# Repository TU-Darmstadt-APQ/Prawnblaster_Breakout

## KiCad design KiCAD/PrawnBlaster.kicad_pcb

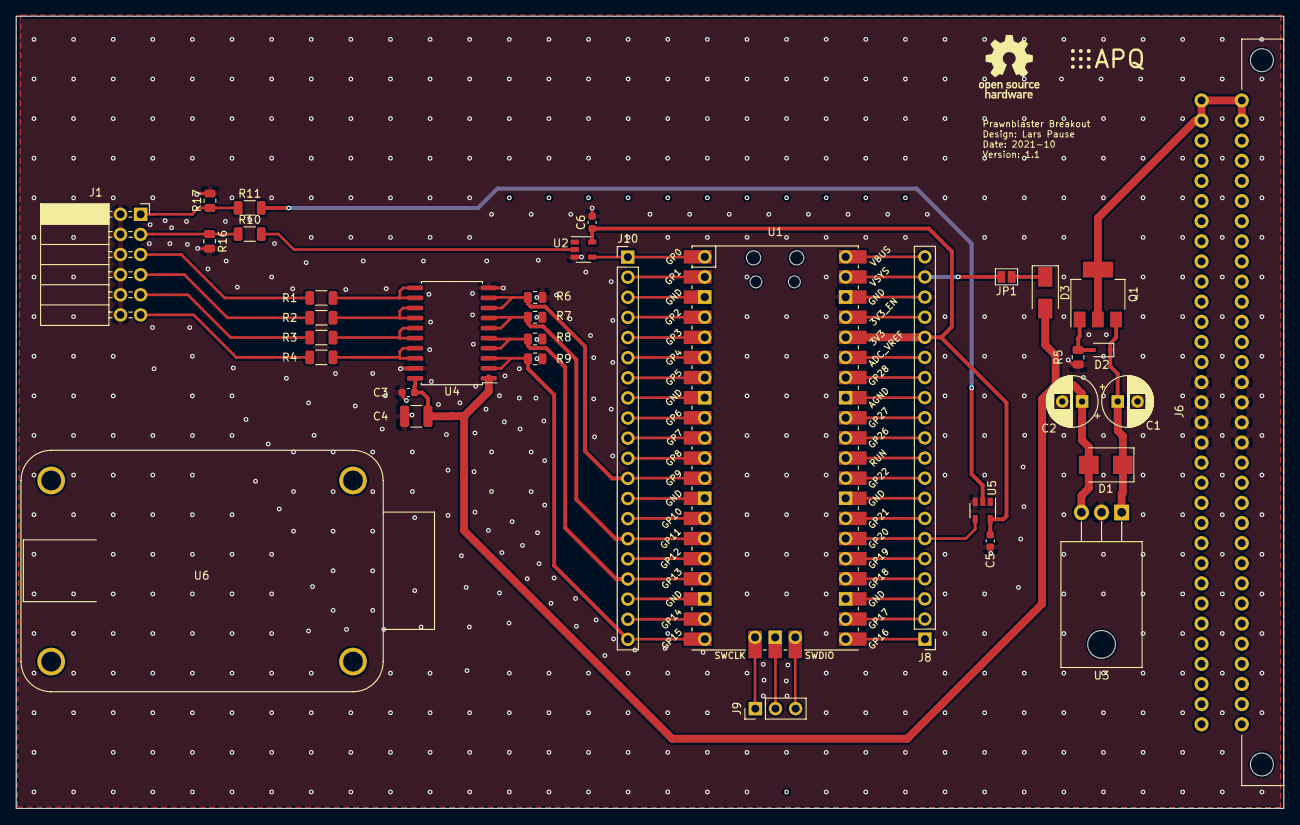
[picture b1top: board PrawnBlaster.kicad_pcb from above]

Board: 2 copper layers, 160.0 x 100.0 mm, 37 parts (0 on the bottom side), 60 nets.

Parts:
C1, C2: 47u; CP_Radial_D6.3mm_P2.50mm
C3, C5, C6: 100n; C_0603_1608Metric
C4: 10u; C_1210_3225Metric
D1: D; D_SMB
D2: MM3Z15VST1G; D_SOD-323
D3: D_Schottky; D_SMA
J1: Conn_02x06_Odd_Even; PinSocket_2x06_P2.54mm_Horizontal
J6: C64AC; Socket_DIN41612-CaseC1-AC-Male-64Pin-2rows
J8, J10: Conn_01x20_Male; PinHeader_1x20_P2.54mm_Vertical
J9: Conn_01x03_Male; PinHeader_1x03_P2.54mm_Vertical
JP1: Jumper_NO_Small; SolderJumper-2_P1.3mm_Open_Pad1.0x1.5mm
LOGO1: Logo_APQ; APQ-Logo_small
LOGO2: Logo_Open_Hardware_Small; OSHW-Logo_7.5x8mm_SilkScreen
Q1: DMP6023LE; SOT-223
R1, R2, R3, R4: 49.9; R_1206_3216Metric
R5: 100k; R_0805_2012Metric
R6, R7, R8, R9: 10k; R_0805_2012Metric
R10, R11: 500; R_1206_3216Metric
R16, R17: 47k; R_0805_2012Metric
U1: Pico; RPi_Pico_SMD_TH
U2: 74LVC1G17; SOT-23-5
U3: 7805; TO-220-3_Horizontal_TabDown
U4: 74ABT245; SOIC-20W_7.5x12.8mm_P1.27mm
U5: 74LVC1G07; SOT-23-5
U6: adafruit_usb_isolator; usb_isolator

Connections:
3_3V_Pico: C5.1, C6.1, J8.16, U1.36, U2.5, U5.5
/Output Buffer/A0: J10.20, R9.1, U1.20, U4.2, U4.3
/Output Buffer/A1: J10.17, R8.1, U1.17, U4.4, U4.5
/Output Buffer/A2: J10.15, R7.1, U1.15, U4.6, U4.7
/Output Buffer/A3: J10.12, R6.1, U1.12, U4.8, U4.9
/Output Buffer/B0: R4.1, U4.17, U4.18
/Output Buffer/B1: R3.1, U4.15, U4.16
/Output Buffer/B2: R2.1, U4.13, U4.14
/Output Buffer/B3: R1.1, U4.11, U4.12
/Output Buffer/Vcc_5V: C2.1, C3.1, C4.1, D1.2, D3.2, U3.3, U4.1, U4.20
/Power Supply/Reverse Polarity Protection/V18: C1.1, D1.1, D2.1, Q1.3, U3.1
/Power Supply/Reverse Polarity Protection/V18_unprot: J6.A1, J6.A2, J6.C1, J6.C2, Q1.2, Q1.4
GND: C1.2, C2.2, C3.2, C4.2, C5.2, C6.2, J1.2, J1.4, J1.6, J1.8, J1.10, J1.12, J6.A15, J6.A16, J6.A17, J6.A18, J6.C15, J6.C16, J6.C17, J6.C18, J8.18, R5.2, R6.2, R7.2, R8.2, R9.2, R16.2, R17.2, U1.38, U2.3, U3.2, U4.10, U4.19, U5.3
unnamed: D2.2, Q1.1, R5.1
unnamed: D3.1, JP1.1
unnamed: J1.1, R11.1, R17.1
unnamed: J1.3, R10.1, R16.1
unnamed: J1.5, R1.2
unnamed: J1.7, R2.2
unnamed: J1.9, R3.2
unnamed: J1.11, R4.2
unnamed: J8.1, U1.21
unnamed: J8.2, U1.22
unnamed: J8.3, U1.23
unnamed: J8.4, U1.24
unnamed: J8.5, U1.25
unnamed: J8.6, U1.26, U5.4
unnamed: J8.7, U1.27
unnamed: J8.8, U1.28
unnamed: J8.9, U1.29
unnamed: J8.10, U1.30
unnamed: J8.11, U1.31
unnamed: J8.12, U1.32
unnamed: J8.13, U1.33
unnamed: J8.14, U1.34
unnamed: J8.15, U1.35
unnamed: J8.17, U1.37
unnamed: J8.19, JP1.2, U1.39
unnamed: J8.20, U1.40
unnamed: J9.1, U1.41
unnamed: J9.2, U1.42
unnamed: J9.3, U1.43
unnamed: J10.1, U1.1, U2.4
unnamed: J10.2, U1.2
unnamed: J10.3, U1.3
unnamed: J10.4, U1.4
unnamed: J10.5, U1.5
unnamed: J10.6, U1.6
unnamed: J10.7, U1.7
unnamed: J10.8, U1.8
unnamed: J10.9, U1.9
unnamed: J10.10, U1.10
unnamed: J10.11, U1.11
unnamed: J10.13, U1.13
unnamed: J10.14, U1.14
unnamed: J10.16, U1.16
unnamed: J10.18, U1.18
unnamed: J10.19, U1.19
unnamed: R10.2, U2.2
unnamed: R11.2, U5.2

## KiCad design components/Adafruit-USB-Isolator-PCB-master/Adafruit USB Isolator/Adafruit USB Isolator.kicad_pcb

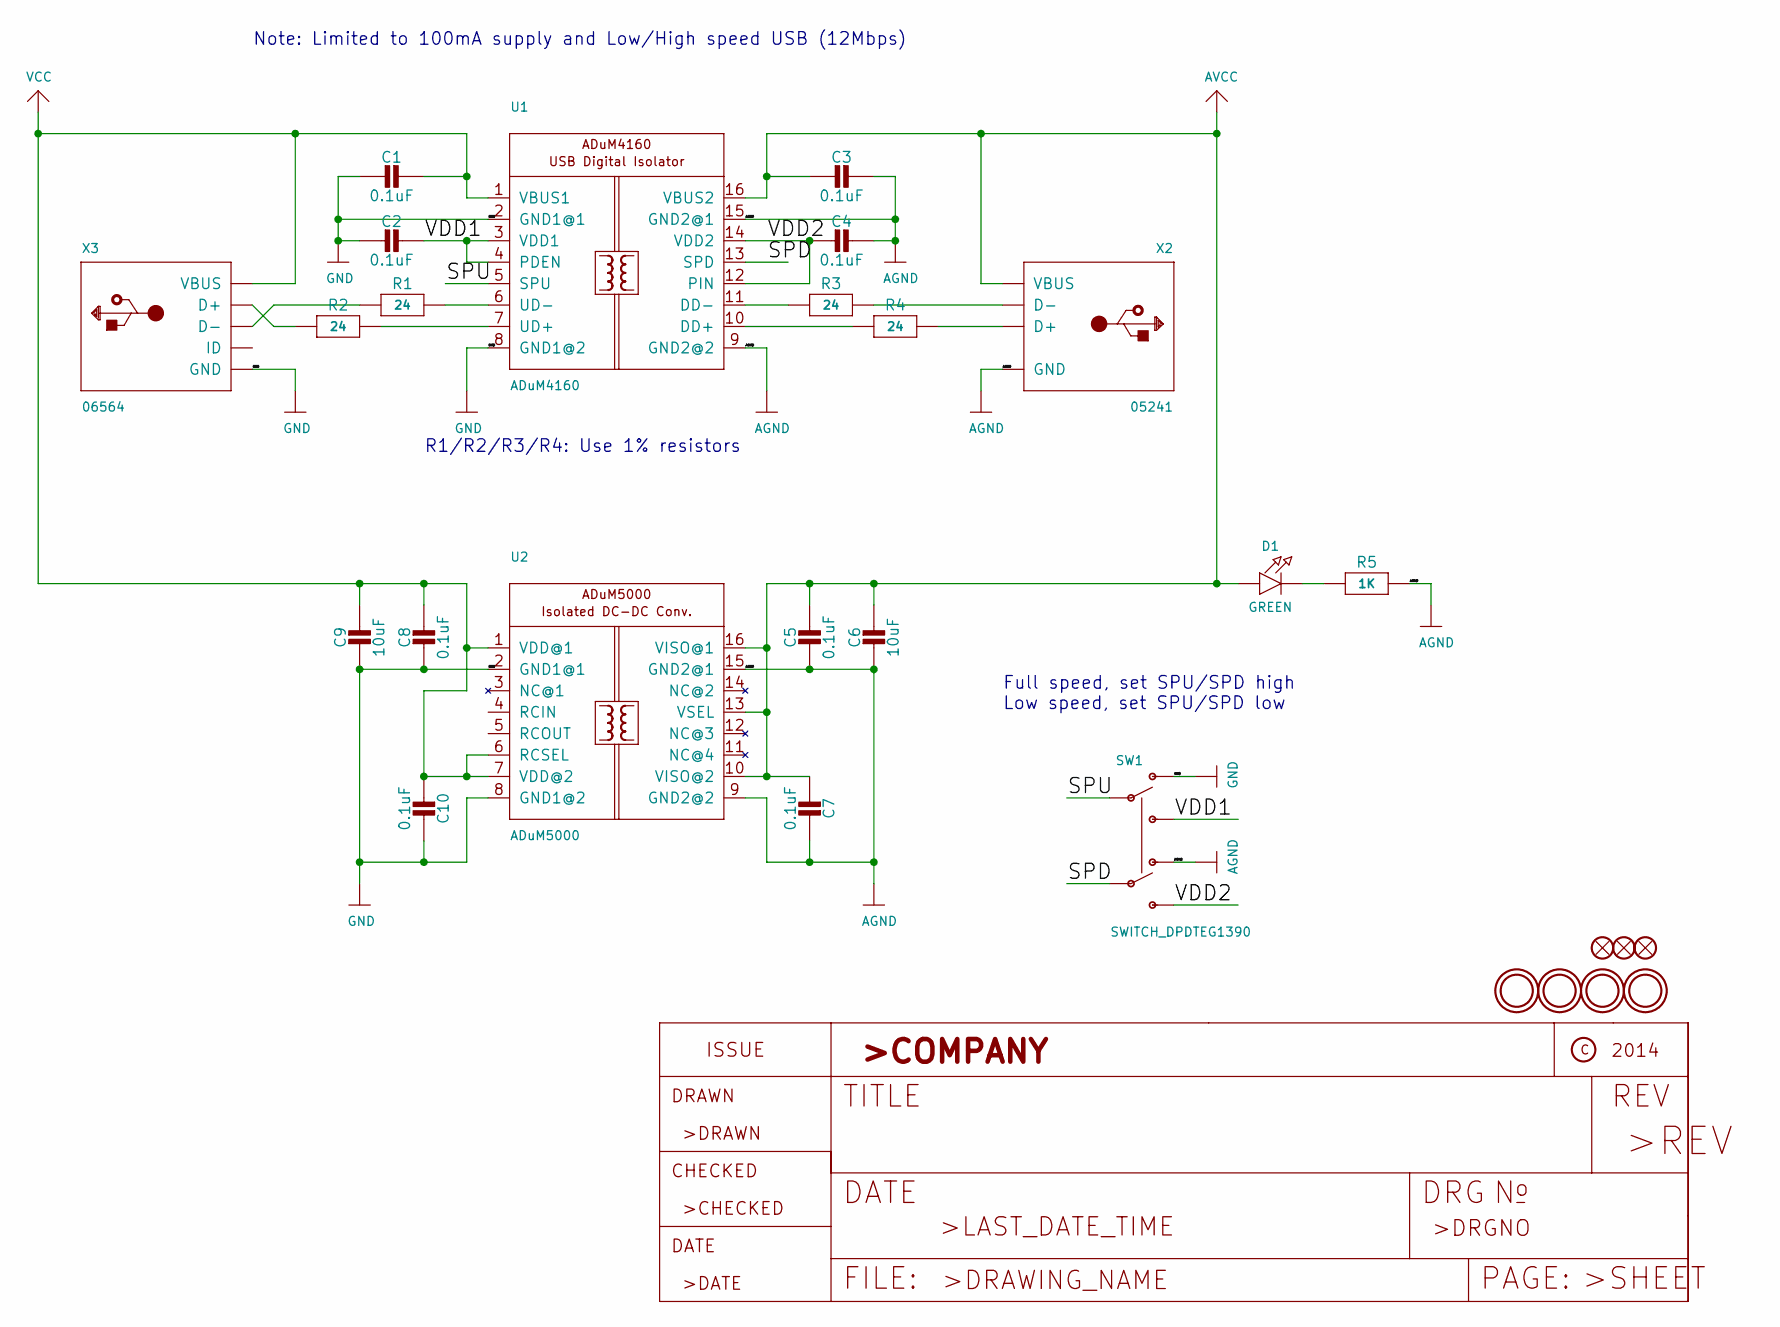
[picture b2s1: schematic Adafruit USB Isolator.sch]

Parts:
C1, C2, C3, C4, C5, C7, C8, C10: 0.1uF; 0805-NO
C6, C9: 10uF; 0805-NO
D1: GREEN; CHIPLED_0805_NOOUTLINE
FID1, FID2, FID3: FIDUCIAL\"\"; FIDUCIAL_1MM
R1, R2, R3: 24; 0805-NO
R4: 24; _0805MP
R5: 1K; 0805-NO
SW1: SWITCH_DPDTEG1390; EG1390
U1: ADuM4160; SOIC16WIDE
U2: ADuM5000; SOIC16WIDE
U$7, U$8, U$9, U$10: MOUNTINGHOLE2.5_THICK; MOUNTINGHOLE_2.5_PLATED_THICK
X2: 05241; USB_HOST-PTH
X3: 06564; USB-MINIB_LARGER

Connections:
/SPD: SW1.P2, U1.13 (SPD)
/SPU: SW1.P1, U1.5 (SPU)
/VDD1: C2.1, SW1.S1, U1.3 (VDD1), U1.4 (PDEN)
/VDD2: C4.2, SW1.S2, U1.12 (PIN), U1.14 (VDD2)
AGND: C3.1, C4.1, C5.2, C6.2, C7.1, R5.2, SW1.O2, U1.9 (GND2@2), U1.15 (GND2@1), U2.9 (GND2@2), U2.15 (GND2@1), X2.GND
AVCC: C3.2, C5.1, C6.1, C7.2, D1.A, U1.16 (VBUS2), U2.10 (VISO@2), U2.13 (VSEL), U2.16 (VISO@1), X2.VBUS
GND: C1.2, C2.2, C8.2, C9.2, C10.1, SW1.O1, U1.2 (GND1@1), U1.8 (GND1@2), U2.2 (GND1@1), U2.8 (GND1@2), X3.GND, X3.GND1 (GND), X3.GND2 (GND), X3.GND3 (GND), X3.GND4 (GND)
unnamed: D1.C, R5.1
unnamed: R1.1, X3.D-
unnamed: R1.2, U1.6 (UD-)
unnamed: R2.1, X3.D+
unnamed: R2.2, U1.7 (UD+)
unnamed: R3.1, U1.11 (DD-)
unnamed: R3.2, X2.D-
unnamed: R4.1, U1.10 (DD+)
unnamed: R4.2, X2.D+
VCC: C1.1, C8.1, C9.1, C10.2, U1.1 (VBUS1), U2.1 (VDD@1), U2.6 (RCSEL), U2.7 (VDD@2), X3.VBUS

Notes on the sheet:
R1/R2/R3/R4: Use 1% resistors
Note: Limited to 100mA supply and Low/High speed USB (12Mbps)
Full speed, set SPU/SPD high Low speed, set SPU/SPD low

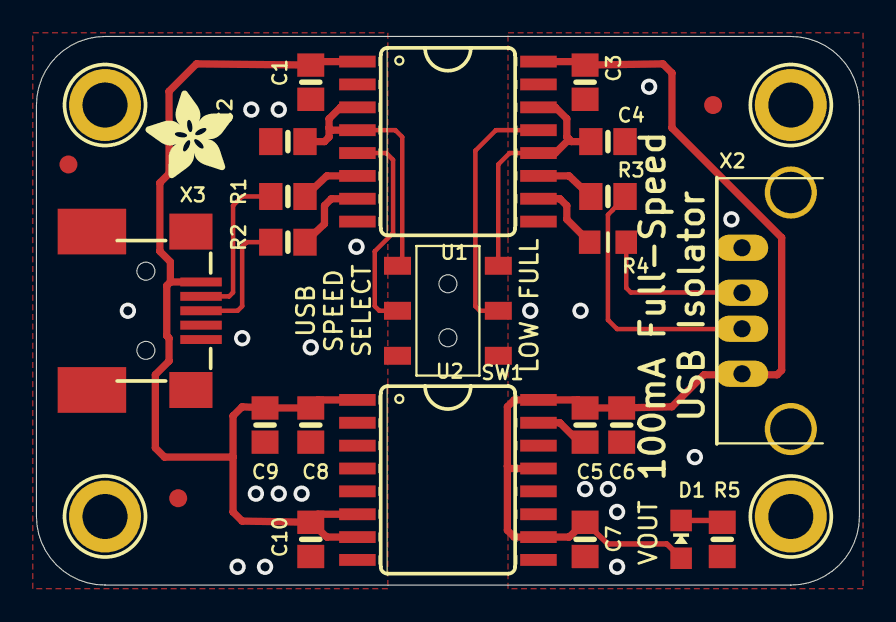
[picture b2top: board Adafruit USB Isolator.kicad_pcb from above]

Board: 2 copper layers, 45.7 x 30.5 mm, 30 parts (0 on the bottom side), 17 nets.

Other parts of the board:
U$14: ADAFRUIT_5MM
U$16: ADAFRUIT_TEXT_30MM

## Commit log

2021-09-16 forked PulseBlaster with 4 outputs
2021-09-16 added pico and external trigger
2021-09-20 Add Pi Pico in project library; create sheets for Pi Pico and ext trig
    Add the Pi Pico library and create sheets for the input buffer (with external trigger input) as well as a pi pico sheet.
2021-09-21 added external trigger
2021-09-21 cleaned up merge artifacts
2021-09-21 rearranged input buffer
2021-09-23 Add GND connections, update authorship
2021-09-24 Add 64Pin Case Power Supply, update PCB dimensions and SMA-Type
    Note: Pi Pico footprint is missing!
2021-09-24 Place 64Pin Connector
2021-10-01 added clock input
2021-10-03 Add PiPico Footprint and route PCB without SMA connectors
    Schematic was updated and routing on PCB was done except for input/output connectors.
2021-10-04 Exchange SMA-connectors with pin-header
    Add pin Header to connect PCB with new Frontpanel PCB. Necessary distances marked. Routing finished.
2021-10-05 Finish routing PCB
2021-10-05 Small updates
2021-10-06 Update MFN, PN and BOM
2021-10-06 Generate gerber and drill files
2021-10-19 Add USB-isolator plus extra power supply; move parts
2021-10-19 Reduce GND-connections to pico to 1
2021-10-19 Update gerber files
2021-10-22 Correct wrong part names and PNs
2021-10-25 Update non-available parts and add missing usb isolator to bom
2021-10-25 Update gerber and drill
2021-10-25 Connected via under R9
2021-10-26 Update Logo position
2021-11-08 Change 74LVC1G07GV to 74LVC1G17GV
    The component 74LVC1G07GV is a drain-open-output device which would need a pull-up resistor to work as intended. Replace by Schmitt-Trigger 74LVC1G17GV.
2021-11-12 Adjust PCB-Layout
    Move Adafruit and Frontpanel connector closer to edge; Untangle Q1 and D3 Silkscreen
2021-11-12 Generate new gerber files
2021-11-12 save pcb

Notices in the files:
KiCAD/PrawnBlaster.kicad_pcb:
Copyright (©) 2020, Patrick Baus
Copyright (©) 2020, Lars Pause
